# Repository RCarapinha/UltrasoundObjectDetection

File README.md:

# Ultrasound Object Detection

Project done in Electronic Laboratory in 1st year of Masters.

## Description

Implement an ultrasonic sensor in a robot, in order to make it detect obstacles that may arise along the way and make it deviate from them autonomously.

The project will be divided into several parts, starting with the assembly of the circuit on the white board, passing to the projection and design of the circuit in the Eagle software and the printing of the board is done to proceed with the soldering of the components.

## Job Done

The board designed was the following:

The final result was the following:

More info on the report.

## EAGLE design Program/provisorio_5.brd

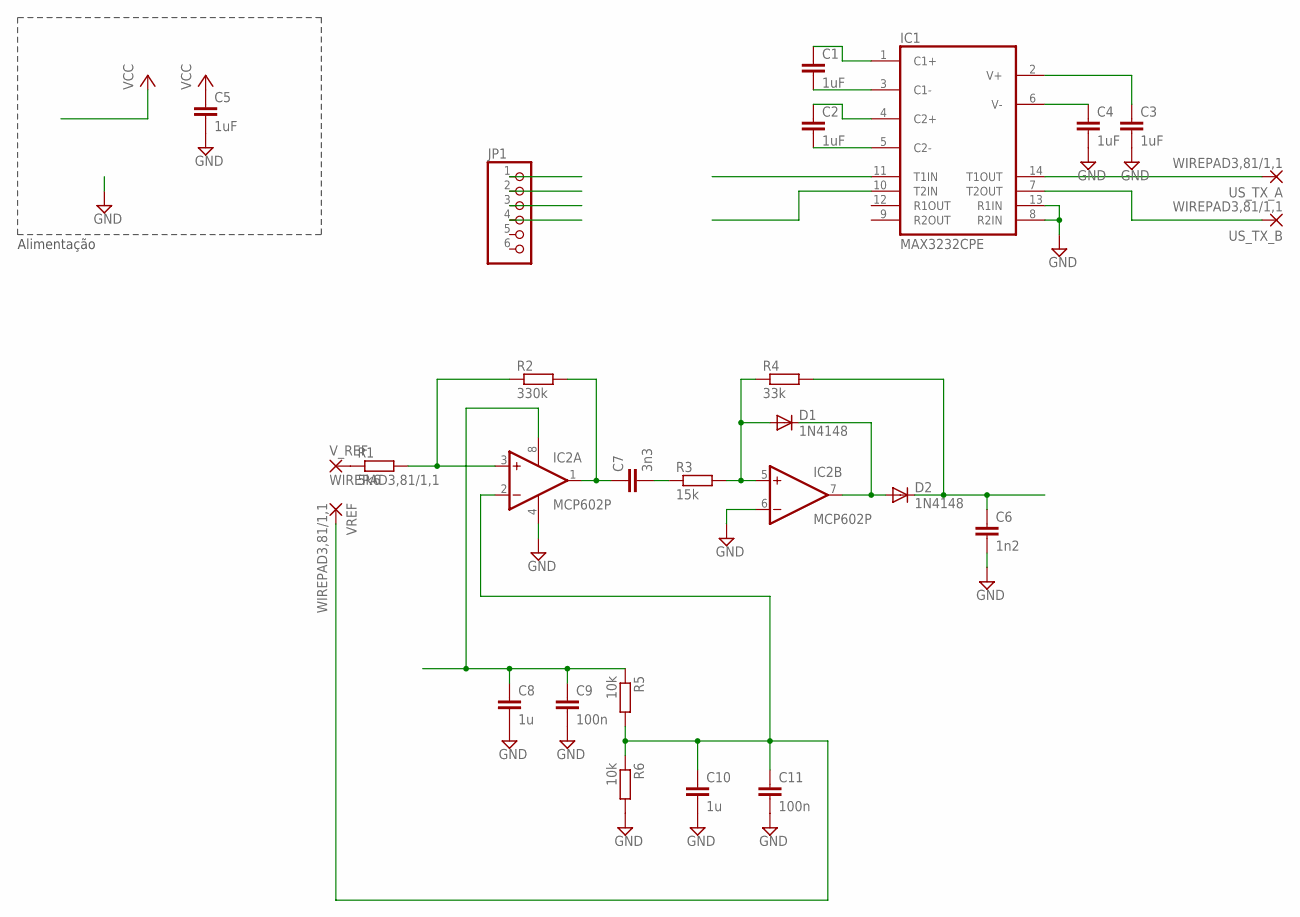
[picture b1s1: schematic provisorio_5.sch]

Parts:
C1, C2, C3, C4, C5: 1uF; C1206K
C6: 1n2; C1206K
C7: 3n3; C1206K
C8, C10: 1u; C1206K
C9, C11: 100n; C1206K
D1, D2: 1N4148; SOD123
IC1: MAX3232CPE; DIL16
IC2: MCP602P; DIL08
JP1: PINHD-1X6; 1X06
R1: 5k6; R1206
R2: 330k; R1206
R3: 15k; R1206
R4: 33k; R1206
R5, R6: 10k; R1206
US_TX_A: WIREPAD3,81/1,1; 3,81/1,1
US_TX_B: WIREPAD3,81/1,1; 3,81/1,1
VREF: WIREPAD3,81/1,1; 3,81/1,1
V_REF: WIREPAD3,81/1,1; 3,81/1,1

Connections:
DIGI1: C6.1, D2.C, IC1.11 (T1IN), JP1.2, R4.2
DIGI2: IC1.10 (T2IN), JP1.1
GND: C3.2, C4.2, C5.2, C6.2, C8.2, C9.2, C10.2, C11.2, IC1.8 (R2IN), IC1.13 (R1IN), IC1.15 (GND), IC2.4 (V-), IC2.6 (-IN), JP1.3, R6.2
unnamed: C3.1, IC1.2 (V+)
unnamed: C2.2, IC1.5 (C2-)
unnamed: C2.1, IC1.4 (C2+)
unnamed: C1.2, IC1.3 (C1-)
unnamed: C1.1, IC1.1 (C1+)
unnamed: C4.1, IC1.6 (V-)
unnamed: IC1.14 (T1OUT), US_TX_A.1
unnamed: IC1.7 (T2OUT), US_TX_B.1
unnamed: IC2.3 (+IN), R1.2, R2.1
unnamed: C7.1, IC2.1 (OUT), R2.2
unnamed: C7.2, R3.1
unnamed: D1.A, IC2.5 (+IN), R3.2, R4.1
unnamed: D1.C, D2.A, IC2.7 (OUT)
unnamed: R1.1, V_REF.1
unnamed: C10.1, C11.1, IC2.2 (-IN), R5.2, R6.1, VREF.1
VCC: C5.1, C8.1, C9.1, IC1.16 (VCC), IC2.8 (V+), JP1.4, R5.1

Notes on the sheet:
Alimentação

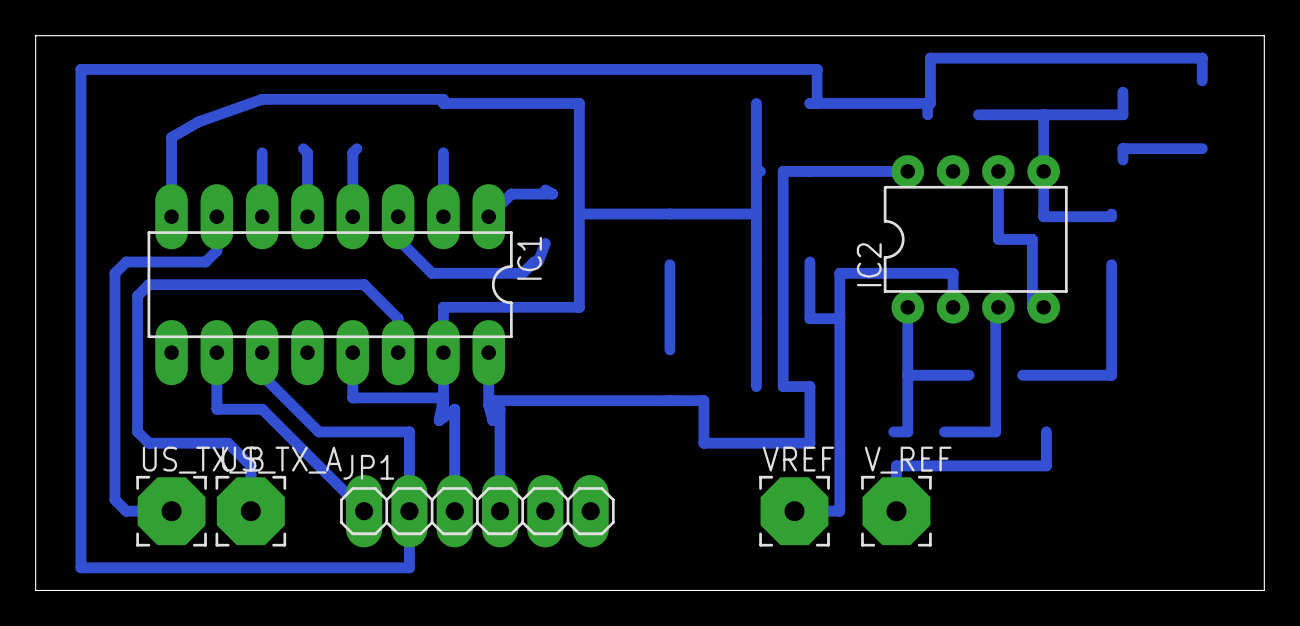
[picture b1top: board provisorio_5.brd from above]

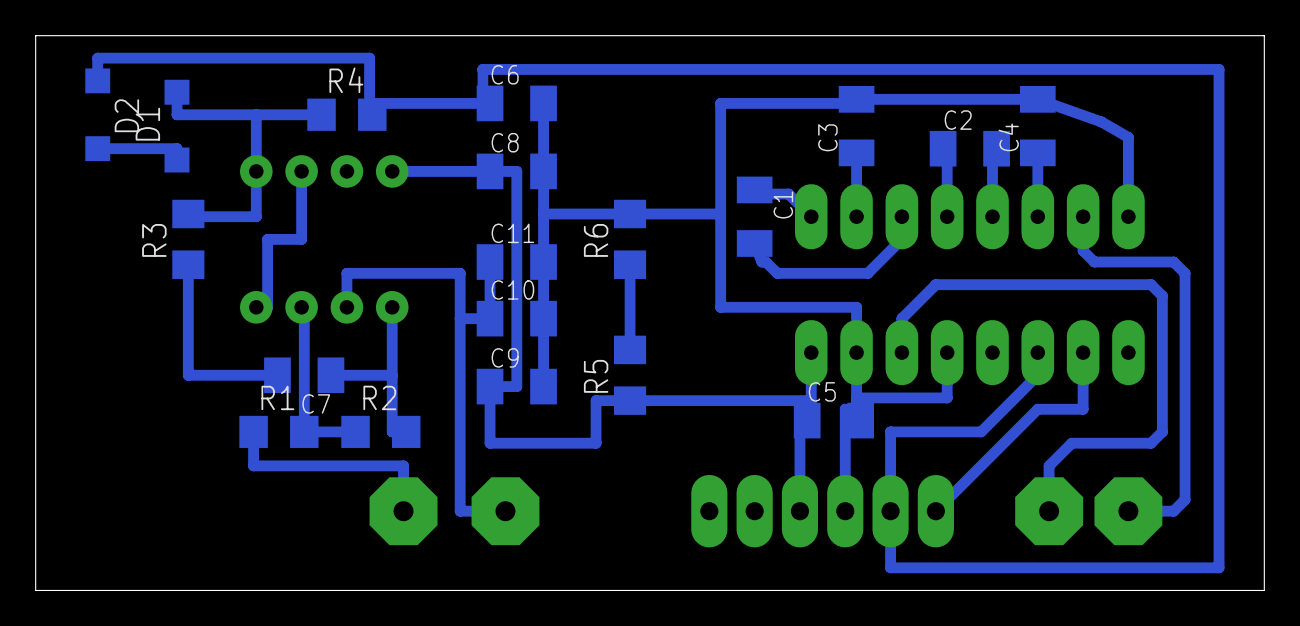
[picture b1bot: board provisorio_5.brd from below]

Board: 2 copper layers, 68.9 x 31.1 mm, 26 parts (19 on the bottom side), 19 nets.

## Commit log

2020-08-01 Images
2020-11-13 Rename README.md to rdm.txt
